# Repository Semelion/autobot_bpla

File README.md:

# Команда Автоботы
## Разработка системы обмена данными в рое дронов с повышенной устойчивостью к препятствиям

## Оглавление
- [Код устройства](#Код_устройства) 
- [JSON файлы запросов](#JSON_файлы_запросов) 
- [GUI](#GUI) 

## Оглавление

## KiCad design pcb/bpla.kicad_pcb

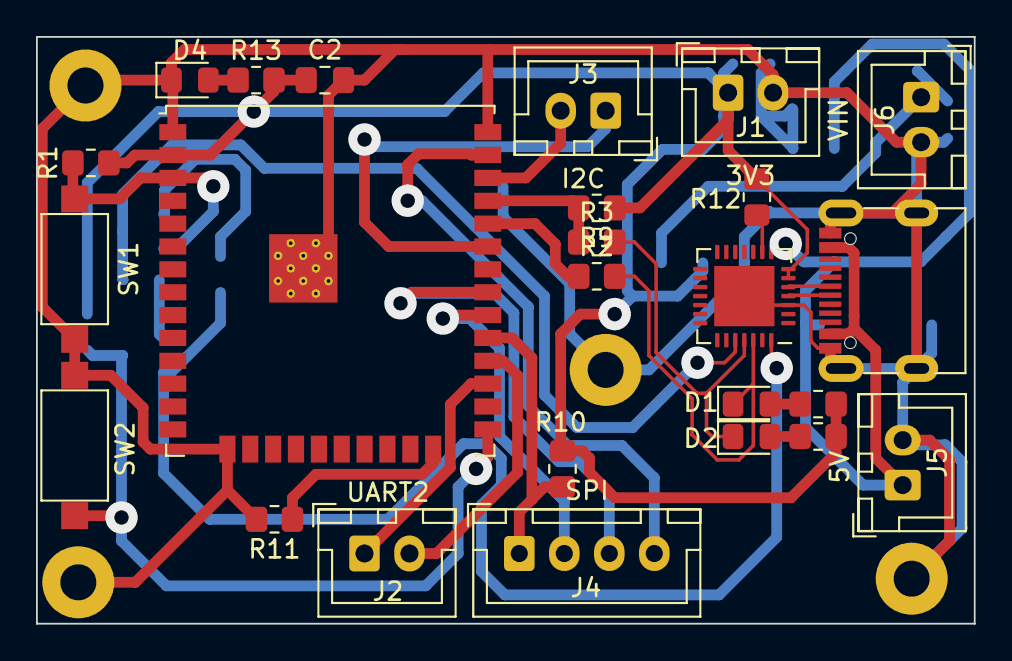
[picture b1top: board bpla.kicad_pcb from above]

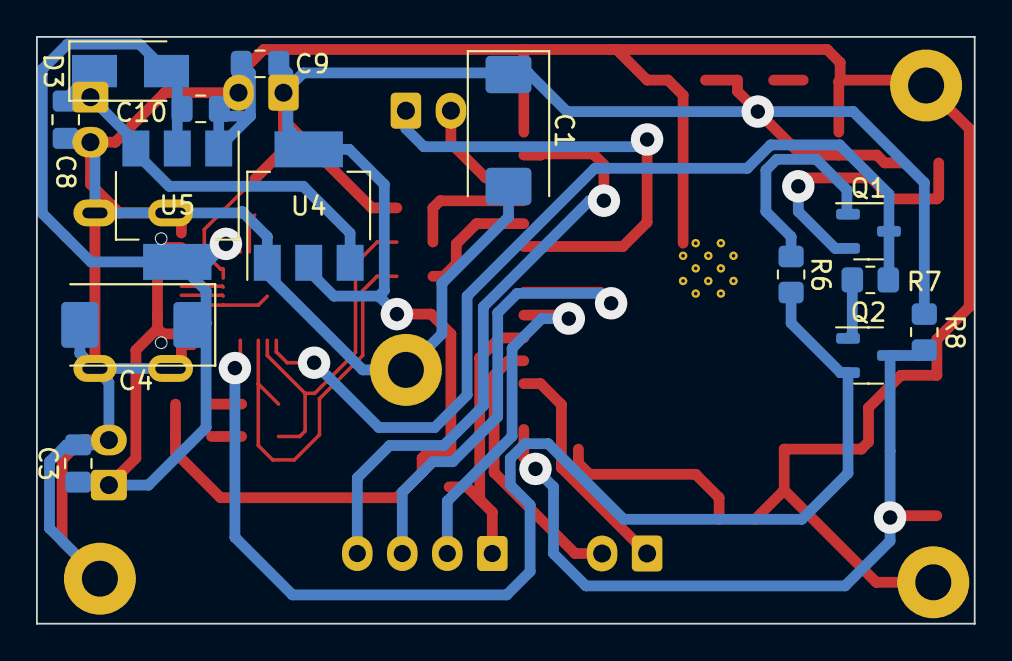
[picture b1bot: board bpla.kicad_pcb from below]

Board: 2 copper layers, 52.1 x 32.6 mm, 39 parts (14 on the bottom side), 29 nets.

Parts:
C1, C4: 10uF; CP_EIA-7343-31_Kemet-D
C2, C3: 0.1uF; C_0805_2012Metric_Pad1.18x1.45mm_HandSolder
C8, C10: 10uF; C_0805_2012Metric_Pad1.18x1.45mm_HandSolder
C9: 1uF; C_0805_2012Metric_Pad1.18x1.45mm_HandSolder
D1, D2, D4: LED; LED_0805_2012Metric_Pad1.15x1.40mm_HandSolder
D3: D_Schottky; D_SMA
J1: 3V3; JST_XH_B2B-XH-A_1x02_P2.50mm_Vertical
J2: UART2; JST_XH_B2B-XH-A_1x02_P2.50mm_Vertical
J3: I2C; JST_XH_B2B-XH-A_1x02_P2.50mm_Vertical
J4: SPI; JST_XH_B4B-XH-A_1x04_P2.50mm_Vertical
J5: 5V; JST_XH_B2B-XH-A_1x02_P2.50mm_Vertical
J6: VIN; JST_XH_B2B-XH-A_1x02_P2.50mm_Vertical
P1: USB_C_Plug; USB_C_Receptacle_G-Switch_GT-USB-7010ASV
Q1, Q2: 2SC1623; SOT-23-3
R1, R6, R7, R8, R9, R10, R11: 10K; R_0805_2012Metric_Pad1.20x1.40mm_HandSolder
R2, R3: 300R; R_0805_2012Metric_Pad1.20x1.40mm_HandSolder
R4, R5: 680R; R_0805_2012Metric_Pad1.20x1.40mm_HandSolder
R12: 4.7K; R_0805_2012Metric_Pad1.20x1.40mm_HandSolder
R13: 220R; R_0805_2012Metric_Pad1.20x1.40mm_HandSolder
SW1, SW2: SW_MEC_5G; SW_SPST_CK_RS282G05A3
U1: ESP32-WROOM-32U
U3: CP2102N-Axx-xQFN28; QFN-28-1EP_5x5mm_P0.5mm_EP3.35x3.35mm
U4: AMS1117-3.3; SOT-223-3_TabPin2
U5: AMS1117-5.0; SOT-223-3_TabPin2

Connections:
+3.3V: C1.1, C2.1, C9.1, J1.1, R1.1, R4.2, R5.2, R8.2, R9.1, R10.1, R12.2, R13.2, U1.2 (VDD), U3.6 (VDD), U3.7 (VREGIN), U4.2 (VO)
+5V: C3.1, C4.1, C10.1, D3.2 (A), J5.1, P1.A4 (VBUS), P1.A9 (VBUS), P1.B4 (VBUS), P1.B9 (VBUS), U3.8 (VBUS), U5.2 (VO)
GND: C1.2, C2.2, C3.2, C4.2, C8.2, C9.2, C10.2, D4.1 (K), J1.2, J5.2, J6.2, P1.A1 (GND), P1.A12 (GND), P1.B1 (GND), P1.B12 (GND), P1.S1 (SHIELD), R11.2, SW1.1 (A), SW1.2 (A), SW2.2 (B), U1.1 (GND), U1.15 (GND), U1.38 (GND), U1.39 (GND), U3.3 (GND), U3.29 (GND), U4.1 (GND), U5.1 (GND)
GPIO_0: Q2.3 (E), R8.1, SW2.1 (A), U1.25 (IO0)
unnamed: C8.1, D3.1 (K), J6.1, U4.3 (VI), U5.3 (VI)
unnamed: D1.1 (K), R2.2, U3.26 (TXD)
unnamed: D1.2 (A), R4.1
unnamed: D2.1 (K), R3.2, U3.25 (RXD)
unnamed: D2.2 (A), R5.1
unnamed: D4.2 (A), R13.1
unnamed: J2.1, U1.27 (IO16)
unnamed: J2.2, U1.28 (IO17)
unnamed: J3.1, U1.33 (IO21)
unnamed: J3.2, U1.36 (IO22)
unnamed: J4.1, R10.2, U1.29 (IO5)
unnamed: J4.2, U1.30 (IO18)
unnamed: J4.3, U1.31 (IO19)
unnamed: J4.4, U1.37 (IO23)
unnamed: P1.A6 (D+), U3.4 (D+)
unnamed: P1.A7 (D-), U3.5 (D-)
unnamed: Q1.1 (B), R6.1
unnamed: Q1.2 (C), R1.2, U1.3 (EN)
unnamed: Q1.3 (E), R7.2, U3.24 (~RTS)
unnamed: Q2.1 (B), R7.1
unnamed: Q2.2 (C), R6.2, U3.28 (~DTR)
unnamed: R2.1, U1.34 (RXD0/IO3)
unnamed: R3.1, R9.2, U1.35 (TXD0/IO1)
unnamed: R11.1, U1.24 (IO2)
unnamed: R12.1, U3.9 (~RST)

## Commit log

2024-11-20 Create ESP_Mesh_Creator
2024-11-21 Create none
